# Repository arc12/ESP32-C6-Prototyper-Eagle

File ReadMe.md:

# ESP32-C6 Prototyper
A PCB for prototyping using an ESP32-C6-WROOM-1(U) module.

The additional circuitry, board layout, and I/O labelling is oriented towards the development of battery-powered sense/logging, potentially with attachment of a radio module via UART for LoRa, NB-IoT, etc. In particular, use of the ULP co-processor is anticipated.

The main I/O at board edge are arranged to support multiple scenarios:
- standard 0.1" header pins, either straight or right angle for insertion into solderless breadboard, with the single row allowing for plenty of free space to work in.
- standard 0.1" header receptacles for "du pont" wire lash-ups or direct plugging of modules.
- JST-EH (or similar or screw connectors for deployed prototypes).

Most of the components connected to GPIOs are optional. The external crystal (and associated capacitors) is also optional but is anticipated as a normal fitting, given the design use cases and the poor time-keeping of the on-chip RC oscillator, so GPIOs 0 and 1 are not brought out (these "pins" are the crystal connections).

## Supporting Elements
The added elements are largely self-evident from the schematic, but some notes...

The U1/U5 circuit provides for measurement of the voltage of the power source (before LDO reduction), using R20/21 voltage divided to bring the ADC intput to within its Vref range. U1 allows the ADC to be used for another input when not sampling Vin. U5 ensures that there is not a continuous trickle through the potential divider during deep sleep.

Circuits around Q1 and U4 are intended to allow GPIOs to switch Vcc on/off to suppress unwanted peripheral current drain. The load switch (U4) is probably the best option for heavier loads and includes an optional capacitor (C10) if the current surge causes problems. Higher current load switches with the same pinout are available. The circuit around U4 (fed by GPIO22), output to P13 can be directly connected to the UART0 headers via J12. Less demanding loads can use the circuit around Q1, which is driven active-low by GPIO23 and controls output to P10. The An optional resistor in the MCU-MOSFET connection is shorted out; cut the trace and add a resistor if the ESP32 drive circuit and MOSFET gate capacitance cause problems. J18 allows for either temporary bypassing if header pins are fitted, or for P10 to be converted to permanent power out points if a wire link is used.

Pull-down resistors on U4 and U5 could probably be omitted if GPIO15 is set to "hold" the outputs low on deep sleep. Otherwise they are essential to avoid ambient pickup.

Circuits around Q2/3 are intended for driving loads which have a current exceeding the ESP32 output drivers. An optional capacitor is accommodated if the current surge causes problems. J6/7 can be used to use GPIO4/5 as inputs (these GPIOs are available to the ULP so can be used for counting or event-driven task initiation) or as outputs driven direct from the ESP32 (in which case R12/3 can be co-opted as load current control resistors). These  GPIOs are also usable for LP UART, and are the only ones which can, with R12/3 and J6/7 as shorts. R4 and R7 are for load current control and J8/9 are present to allow for quick-change of resistance when breadboarding.

The header marked "CTRL" is intended for a push button to bring the ESP32 out of deep sleep into e.g. offering a WiFi SoftAP for data off-loading, configuration, etc. This is, therefore, a LP GPIO. GPIO15 is intended for conditional signalling while awake and has a series resistor for convenience. These can, of course, be co-opted to generic GPIO use. LP_GPIO3 has a pull-up resistor option for use as a wake-from-sleep push button input.

The GPIO-A1 header may be used for SPI comms (signals routed via GPIO matrix, so not suitable for very fast comms) but also contains all the signal lines for SD card connection, although the PCB traces are rather long for high speed use.

J14 is intended for measuring current consumption.

UART0, brought out as HP_UART, is intended for LoRa or NB-IoT modules, which would be powered from the main board. GPIO22 can be used to switch power off as these are likely to be quite power hungry if they do not have a good sleep mode (and in any case, the main use case has the ESP32 in deep sleep most of the time so even a small quiescent current to such modules is unwelcome. J12 controls whether or not a switched power supply is connected and may also be left compeltely open if a USB-Seriel adapter is connected here (the pinout of P7 is made to suit common adapters) and should not power the board.

J15/16 are intended for attaching removable jumpers, as configuration setting inputs. They are not connected to any GPIO but have an adjacent hole to allow for a flying wire to be easily soldered and any free GPIO used.

## ULP Notes
GPIOs for the ULP to count events or to trigger a wake-up of the HP CPU must use the LP GPIO (0-7), which are marked with an asterisk on the PCB.

I2C (and UART, although that is not specifically brought to a header) capabilities for the ULP are reduced compared to the main CPU.

## Programming and Debugging
Uses the USB CDC and JTAG adapter built into the ESP32-C6. Use of UART0 for stdout logging should be disabled using the following sdkconfig:
```
CONFIG_ESP_CONSOLE_USB_SERIAL_JTAG=y
CONFIG_ESP_CONSOLE_SECONDARY_NONE=y
CONFIG_ESP_CONSOLE_USB_SERIAL_JTAG_ENABLED=y
```

This still leaves some output to UART0 at boot time, which can be suppressed by "strapping" GPIO 15 at boot time or by blowing an eFuse.

The "pins" which can be directly connected to the JTAG controller are xxxxxxxxxxxxxxxxxxxxxxxxxxxx

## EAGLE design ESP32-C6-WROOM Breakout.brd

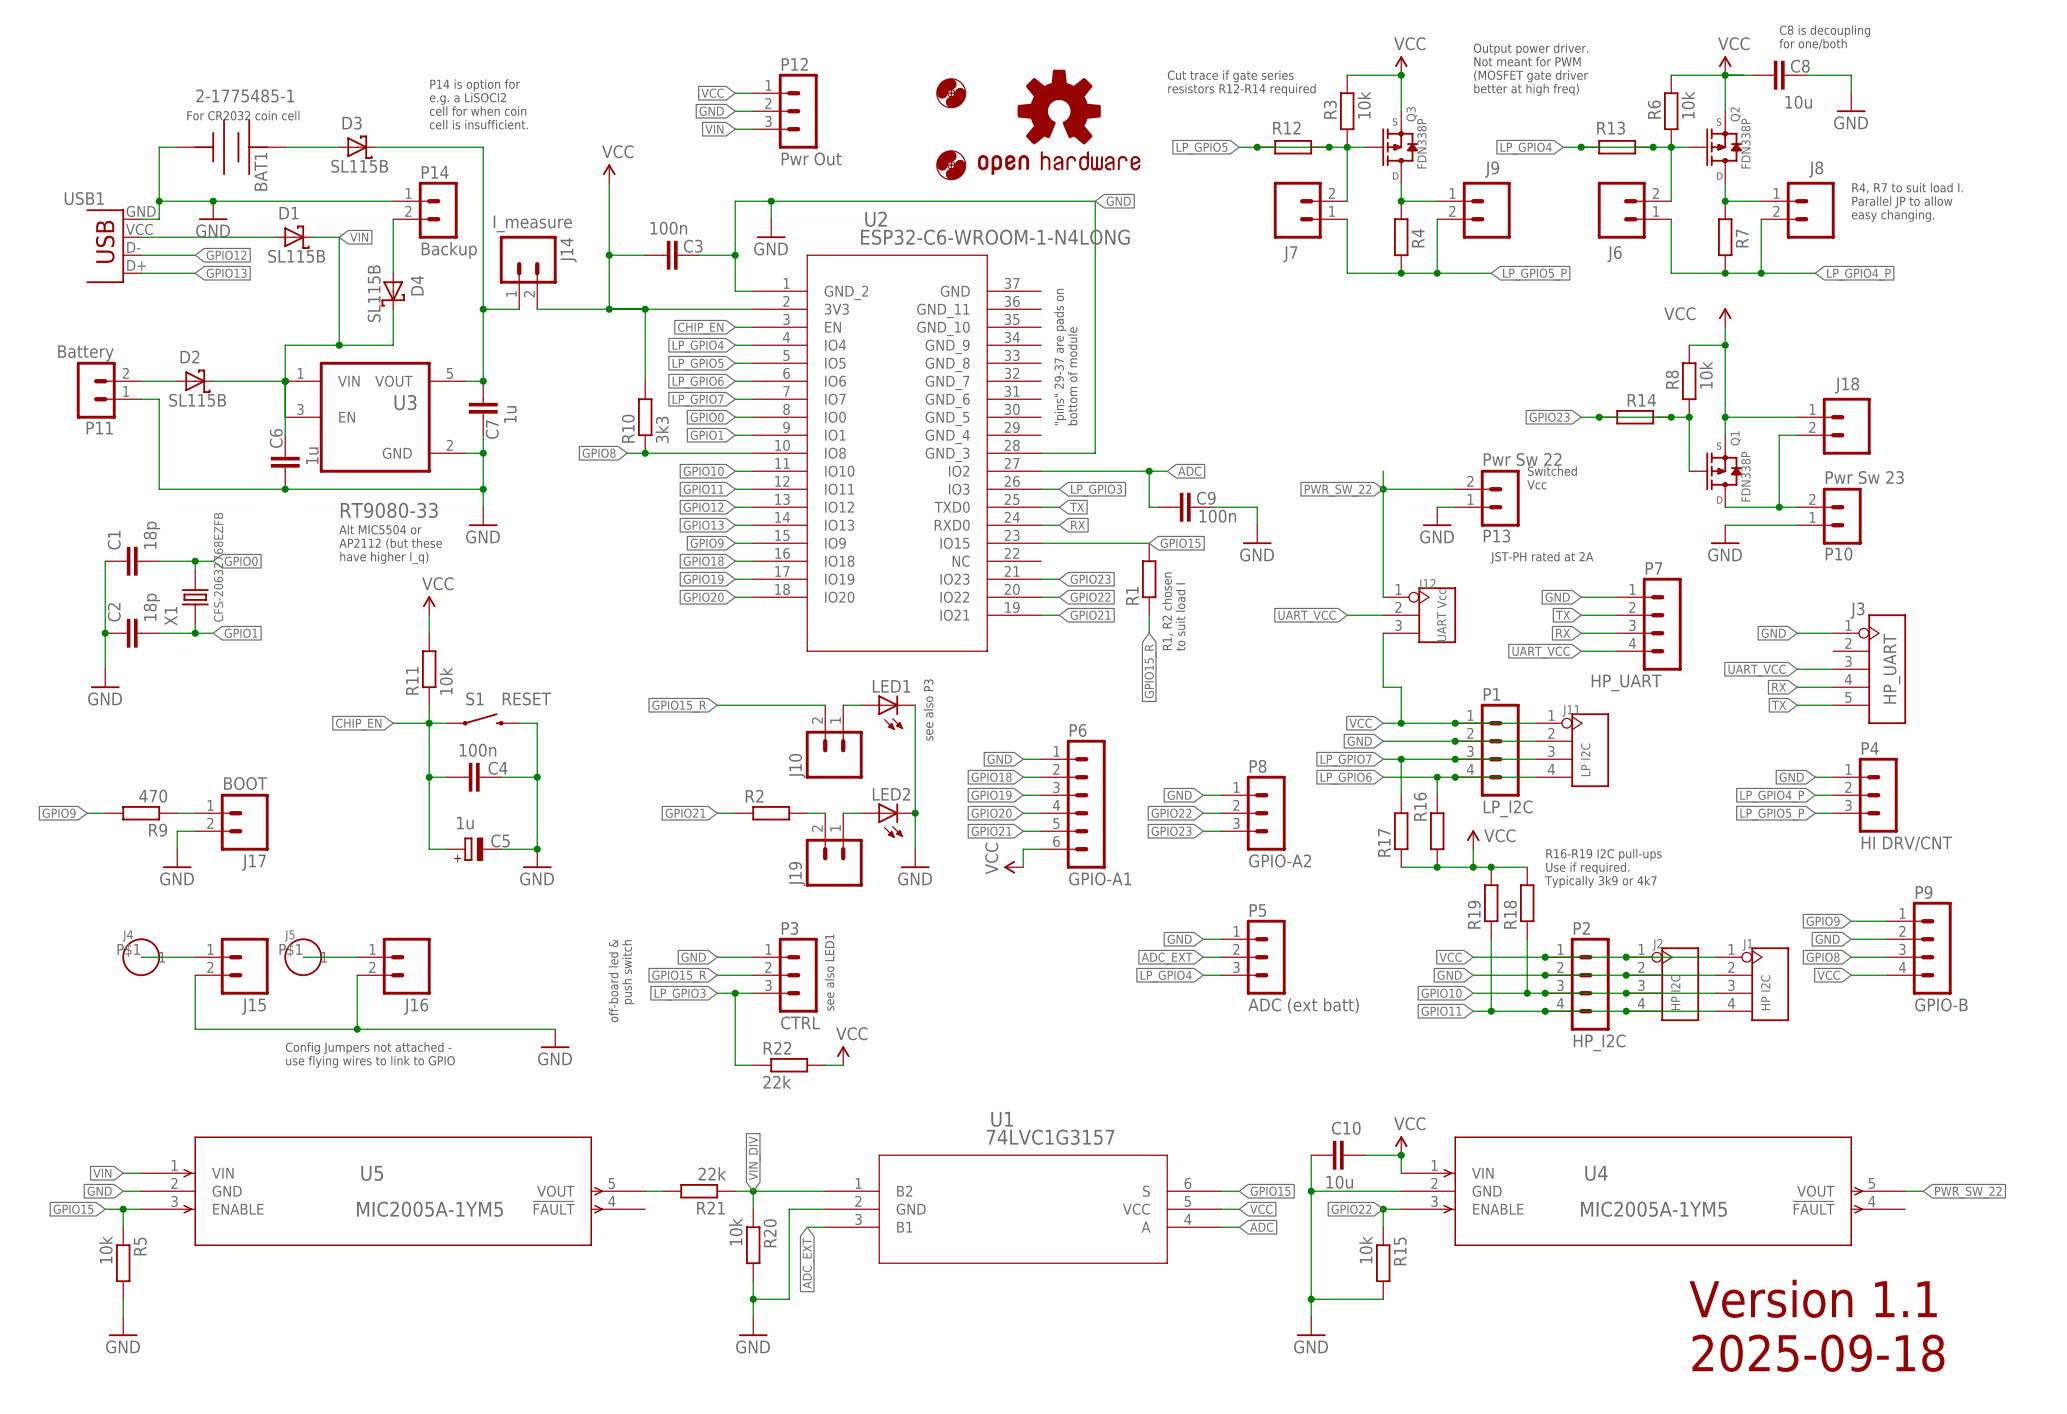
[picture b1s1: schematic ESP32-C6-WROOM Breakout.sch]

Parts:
BAT1: 2-1775485-1; COIN_2-1775485-1_TEC
C1, C2: 18p; 1206
C3, C4, C9: 100n; 1206
C5: 1u; E2,5-5
C6, C7: 1u; 1206
C8, C10: 10u; 1206
D1, D2, D3, D4: SL115B; DO-214AA
H1, H2: MOUNT-HOLE2.8; 2,8
J1, J2: HP I2C; 4P-2.54-80/40MIL
J3: HP_UART; 5P-2.54
J4, J5: HEADER-1P-35; 1P-65/35MIL
J6, J7, J8, J9, J10, J15, J16, J18, J19: HEADER-1X2PPTH; 1X02
J11: LP I2C; 4P-2.54-80/40MIL
J12: UART Vcc; 3P-2.54
J14: I_measure; 1X02
J17: BOOT; 1X02
LED1, LED2: LED1206; LED-1206
LOGO1: OSHW-LOGOL; OSHW-LOGO-L
P1: LP_I2C; B4B-EH-A
P2: HP_I2C; B4B-EH-A
P3: CTRL; B3B-EH-A
P4: HI DRV/CNT; B3B-EH-A
P5: ADC (ext batt); B3B-EH-A
P6: GPIO-A1; B6B-EH-A
P7: HP_UART; B4B-EH-A
P8: GPIO-A2; B3B-EH-A
P9: GPIO-B; B4B-EH-A
P10: Pwr Sw 23; B2B-PH-K
P11: Battery; B2B-PH-K
P12: Pwr Out; B3B-PH-K
P13: Pwr Sw 22; B2B-PH-K
P14: Backup; B2B-PH-K
Q1, Q2, Q3: FDN338P; SOT23_LONG
R1, R2, R4, R7, R12, R13, R14: R-EU_; 1206
R3, R5, R6, R8, R11, R15, R20: 10k; 1206
R9: 470; 1206
R10: 3k3; 1206
R16, R17, R18, R19: 4k7; 1206
R21, R22: 22k; 1206
S1: RESET; TACTILE-PTH
U1: 74LVC1G3157; DBV6
U2: ESP32-C6-WROOM-1-N4LONG; MOD28_ESP32-C6-WROOM-1_LONG
U3: RT9080-33; SOT95-LONGPADS
U4, U5: MIC2005A-1YM5; SOT-23-5_M5_MCH-M
USB1: USB-FCI_SMD_LONG***; FCI_USB_B_SMD_LONG
X1: CFS-20632768EZFB; TC26H

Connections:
ADC: C9.1, U1.4 (A), U2.27 (IO2)
ADC_EXT: P5.2, U1.3 (B1)
CHIP_EN: C4.2, C5.+, R11.1, S1.1, U2.3 (EN)
GND: BAT1.2 (NEG), C1.1, C2.1, C3.2, C4.1, C5.-, C6.2, C7.2, C8.2, C9.2, C10.1, J1.2, J2.2, J3.1, J11.2, J15.2, J16.2, J17.2, LED1.C, LED2.C, P1.2, P2.2, P3.1, P4.1, P5.1, P6.1, P7.1, P8.1, P9.2, P10.1, P11.1, P12.2, P13.1, P14.1, R5.2, R15.2, R20.2, S1.3 (2), U1.2 (GND), U2.1 (GND_2), U2.28 (GND_3), U3.2 (GND), U4.2 (GND), U5.2 (GND), USB1.GND
GPIO0: C1.2, U2.8 (IO0), X1.2
GPIO1: C2.2, U2.9 (IO1), X1.1
GPIO8: P9.3, R10.1, U2.10 (IO8)
GPIO9: P9.1, R9.2, U2.15 (IO9)
GPIO10: J1.3, J2.3, P2.3, R18.1, U2.11 (IO10)
GPIO11: J1.4, J2.4, P2.4, R19.1, U2.12 (IO11)
GPIO12: U2.13 (IO12), USB1.D-
GPIO13: U2.14 (IO13), USB1.D+
GPIO15: R1.2, R5.1, U1.6 (S), U2.23 (IO15), U5.3 (ENABLE)
GPIO15_R: J10.2, P3.2, R1.1
GPIO18: P6.2, U2.16 (IO18)
GPIO19: P6.3, U2.17 (IO19)
GPIO20: P6.4, U2.18 (IO20)
GPIO21: P6.5, R2.1, U2.19 (IO21)
GPIO22: P8.2, R15.1, U2.20 (IO22), U4.3 (ENABLE)
GPIO23: P8.3, Q1.1 (G), R8.1, R14.1, R14.2, U2.21 (IO23)
LP_GPIO3: P3.3, R22.1, U2.26 (IO3)
LP_GPIO4: J6.2, P5.3, Q2.1 (G), R6.1, R13.1, R13.2, U2.4 (IO4)
LP_GPIO4_P: J6.1, J8.2, P4.2, R7.2
LP_GPIO5: J7.2, Q3.1 (G), R3.1, R12.1, R12.2, U2.5 (IO5)
LP_GPIO5_P: J7.1, J9.2, P4.3, R4.2
LP_GPIO6: J11.4, P1.4, R16.2, U2.6 (IO6)
LP_GPIO7: J11.3, P1.3, R17.2, U2.7 (IO7)
unnamed: J17.1, R9.1
unnamed: D2.A, P11.2
unnamed: D1.A, USB1.VCC (VBUS)
unnamed: D4.A, P14.2
unnamed: J18.2, P10.2, Q1.3 (D)
unnamed: BAT1.1 (POS), BAT1.3 (POS), D3.A
unnamed: J9.1, Q3.3 (D), R4.1
unnamed: J10.1, LED1.A
unnamed: J5.P$1, J16.1
unnamed: J19.2, R2.2
unnamed: J19.1, LED2.A
unnamed: J8.1, Q2.3 (D), R7.1
unnamed: C7.1, D3.C, J14.1, U3.5 (VOUT)
unnamed: R21.2, U5.5 (VOUT)
unnamed: J4.P$1, J15.1
PWR_SW_22: J12.1, P13.2, U4.5 (VOUT)
RX: J3.4, P7.3, U2.24 (RXD0)
TX: J3.5, P7.2, U2.25 (TXD0)
UART_VCC: J3.3, J12.2, P7.4
VCC: C3.1, C8.1, C10.2, J1.1, J2.1, J11.1, J12.3, J14.2, J18.1, P1.1, P2.1, P6.6, P9.4, P12.1, Q1.2 (S), Q2.2 (S), Q3.2 (S), R3.2, R6.2, R8.2, R10.2, R11.2, R16.1, R17.1, R18.2, R19.2, R22.2, U1.5 (VCC), U2.2 (3V3), U4.1 (VIN)
VIN: C6.1, D1.C, D2.C, D4.C, P12.3, U3.1 (VIN), U3.3 (EN), U5.1 (VIN)
VIN_DIV: R20.1, R21.1, U1.1 (B2)

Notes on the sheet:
"pins" 29-37 are pads on bottom of module
JST-PH rated at 2A
off-board led & push switch
Output power driver. Not meant for PWM (MOSFET gate driver better at high freq)
Switched Vcc
Config Jumpers not attached - use flying wires to link to GPIO
Alt MIC5504 or AP2112 (but these have higher I_q)
Cut trace if gate series resistors R12-R14 required
R4, R7 to suit load I. Parallel JP to allow easy changing.
R1, R2 chosen to suit load I
R16-R19 I2C pull-ups Use if required. Typically 3k9 or 4k7
For CR2032 coin cell
see also P3
see also LED1
P14 is option for e.g. a LiSOCl2 cell for when coin cell is insufficient.
C8 is decoupling for one/both
Version 1.1 2025-09-18

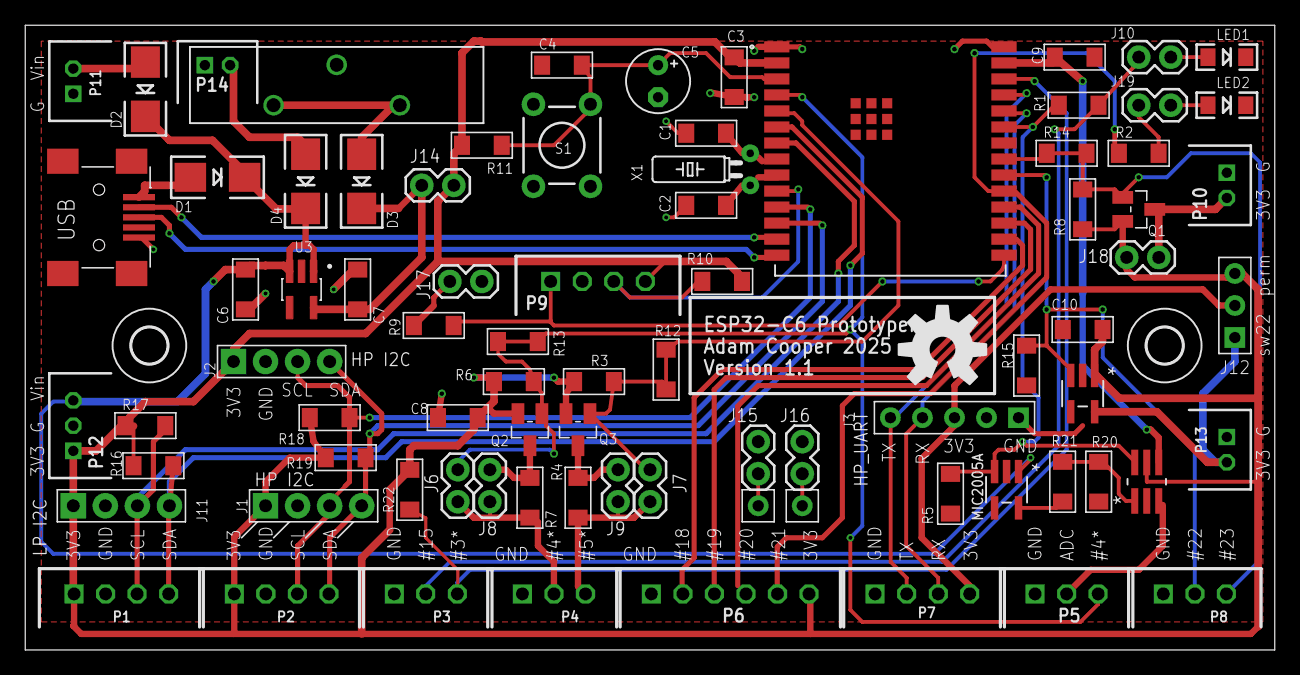
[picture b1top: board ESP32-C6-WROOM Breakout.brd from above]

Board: 2 copper layers, 99.0 x 49.5 mm, 86 parts (1 on the bottom side), 49 nets.

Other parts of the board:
LOGO2: OSHW-LOGOL; OSHW-LOGO-L

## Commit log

2025-05-01 gitignore + WIP (close to candidate v1)
2025-05-01 WIP getting there
2025-05-02 move ADC and add o/p drive caps
2025-05-03 32kHz crystal ground plane separation
2025-05-03 draft wip readme
2025-05-29 close to v1 rev
2025-05-31 Pre-panelisation final v1
2025-05-31 tweak
2025-05-31 Panelised board and gerbers for seeed
2025-09-18 v1.1 essentially completed
2025-09-18 pre v1.1 release cleandown
2025-09-18 prepared for panelisation process
2025-09-18 v1.1 panelised board and gerbers as sent to Seeed
2025-09-18 minor tweaks with no electrical effect

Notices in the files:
parts and their libraries:
con-jst-ph: Copyright (C) 2016, Bob Starr
COPYRIGHT: Copyright (C) 2025 Ultra Librarian. All rights reserved.
